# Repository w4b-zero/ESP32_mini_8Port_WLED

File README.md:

# ESP32_mini_8Port_WLED
<p align="center">
               
[<img src="https://img.shields.io/github/v/tag/w4b-zero/ESP32_mini_8Port_WLED?label=Relase&logo=data%3Aimage%2Fpng%3Bbase64%2CiVBORw0KGgoAAAANSUhEUgAAABgAAAAYCAYAAADgdz34AAABhGlDQ1BJQ0MgcHJvZmlsZQAAKJF9kT1Iw1AUhU9TtVIqHewg4pChOlkQFXHUKhShQqgVWnUweekfNDEkKS6OgmvBwZ%2FFqoOLs64OroIg%2BAPi6uKk6CIl3pcUWsR44fE%2Bzrvn8N59gNCoMs3qGgM03TYzqaSYy6%2BIoVf0IIgoAgjLzDJmJSkN3%2Fq6pz6quwTP8u%2F7s%2FrUgsWAgEg8wwzTJl4nntq0Dc77xDFWllXic%2BJRky5I%2FMh1xeM3ziWXBZ4ZM7OZOeIYsVjqYKWDWdnUiCeJ46qmU76Q81jlvMVZq9ZY6578hZGCvrzEdVpDSGEBi5AgQkENFVRhI0G7ToqFDJ0nffyDrl8il0KuChg55rEBDbLrB%2F%2BD37O1ihPjXlIkCXS%2FOM7HMBDaBZp1x%2Fk%2BdpzmCRB8Bq70tn%2BjAUx%2Fkl5va%2FEjILoNXFy3NWUPuNwBBp4M2ZRdKUhLKBaB9zP6pjzQfwuEV725tc5x%2BgBkaVbpG%2BDgEBgpUfaaz7t7O%2Bf2b09rfj%2FJPHJjkWAKcAAAAAlwSFlzAAAN1wAADdcBQiibeAAAAAd0SU1FB%2BcGAw8EJudd3BAAAAEvSURBVEjHtZYxTsQwEEXfRIgNzbZcBIkjQE2FqFIimmVPAFeggRPQoaViQwsNBfSIkwAS2k%2FjIBMSx86akSJFk8k8%2Fz%2BOFfjnsOZG0hQ4Arb9fCsEvAE3ZvYVTZE0lfSq%2BLiTtBWtQNIxcAV8AM9upV2xCey69%2B6BAzN7j1Fw5lb2GFE7k7Ry9fWQkqLD47Bkswtg7mr3gdsQpGgPO8rX35C9EKQYsKOQVLmrGIAsJJVDM3ho5Stv51RjZjLKooGZLP7YJem8R0GvRUlKPIue1jkWOiCT5sGhS64kzTJC5k1yw33%2BuSC163XtJ0tJSw9ymk1BLkir%2BfJnBjkgHQMuQ8VJkNQDMAkyqnksJMmWVMhaK4%2BA1Nma90DkbcUy6q8iEjIBToAd4AW4NLPP0DvfUiJxtCJLzP0AAAAASUVORK5CYII%3D&style=plastic">](https://github.com/w4b-zero/ESP32_mini_8Port_WLED/releases)
 &nbsp; 
 &nbsp; 
 &nbsp; 
 &nbsp; 
[![IMAGE_ALT](https://img.shields.io/github/languages/code-size/w4b-zero/ESP32_mini_8Port_WLED?style=plastic&logo=data%3Aimage%2Fpng%3Bbase64%2CiVBORw0KGgoAAAANSUhEUgAAABgAAAAYCAYAAADgdz34AAABhWlDQ1BJQ0MgcHJvZmlsZQAAKJF9kT1Iw0AcxV9TtSIVBTuIOASpgmBBVMRRq1CECqFWaNXB5NIvaNKQpLg4Cq4FBz8Wqw4uzro6uAqC4AeIq4uToouU%2BL%2Bk0CLWg%2BN%2BvLv3uHsHCNUi06y2cUDTbTMRi4qp9KoYeEUH%2FOjFEEZlZhlzkhRHy%2FF1Dx9f7yI8q%2FW5P0e3mrEY4BOJZ5lh2sQbxNObtsF5nzjE8rJKfE48ZtIFiR%2B5rnj8xjnnssAzQ2YyMU8cIhZzTaw0McubGvEUcVjVdMoXUh6rnLc4a8Uyq9%2BTvzCY0VeWuU5zEDEsYgkSRCgoo4AibERo1UmxkKD9aAv%2FgOuXyKWQqwBGjgWUoEF2%2FeB%2F8LtbKzs54SUFo0D7i%2BN8DAOBXaBWcZzvY8epnQD%2BZ%2BBKb%2FhLVWDmk%2FRKQwsfAT3bwMV1Q1P2gMsdoP%2FJkE3Zlfw0hWwWeD%2Bjb0oDfbdA15rXW30fpw9AkrqK3wAHh8BIjrLXW7y7s7m3f8%2FU%2B%2FsBa05ypE2o5wYAAAAJcEhZcwAADdcAAA3XAUIom3gAAAAHdElNRQfnBgMRBAFU7%2BcBAAABg0lEQVRIx72WsUtbURTGf%2FdhKOpmN5eSwdVOMYUWCkKhVOPgIM1f4JjRNWMnO5R2Lx1FJylth1QdBEFQ3MShVB0FkUihWvx1uYXweGmSl5g7nvu9%2B53vnPMdHgzzqHPqud2fn2rlf2%2BGFMEZcAl87pDLM%2BApsA88BqohhPVuFKjWu8DVI3ZMbah%2F1GoWNumnpCGEX8A8sAN8yiJJ%2Bu1bJFkAdoGP6Z7kJfgdS%2FUwklwDr4BD4N0gCL4At8DFv3ECmkAJeNQKHMlZlgN1BqgA4xnT1XY6jtTXffioHtVkKwghTA%2FavMl9b4ekRd6EuqWupmS%2FVb%2BrE7kJ1MloljLwLYX5CjwBtiOu58YU1RO1qb5og3muXqk%2F1Klemox6rN6opQ6JlCLuuBeCBFgDCkBNLbT5sADUIm4tT5lW1Dt1Ux1N3T1QN6Jh3%2FTqg9bL5bh236fiH2J8OY%2FR0oBZtZyKldXZQTm5kbF39vox2khGFktAMed7i8BZJ5lH5j%2Bn6suh%2Fqn8BbHck7yUqD2nAAAAAElFTkSuQmCC)](https://github.com/w4b-zero/ESP32_mini_8Port_WLED/archive/refs/heads/main.zip) <br> 
 &nbsp; 
 &nbsp; 

</p>

### Eliminated short circuit, corrected schematic & PCB!

PCB and KiCad-Files for a 8Port WLED ESP32_mini Board<br>
</a> <br>
<ul>
<li>Gerber Files</li>
<li>KiCad 7 Project Files</li>
<li>included used Library Files where not in official KiCad-Library for KiCad 7</li>
  </ul>
<br>

## KiCad Symbol Librarys

<ul>
<li>button:SW_PUSH-12mm</li>
<li>button:SW_PUSH-12mm_roundKnob</li>
<li>button:SW_PUSH-12mm_squareKnob</li>
<li>eec:TSOP38238</li>
<li>ESP32_mini:mini_esp32</li>
<li>wemos_mini:WeMos_D1_mini</li>
  </ul>
<br> 

## KiCad Footprints inkl. 3D-Models

<ul>
<li>button:SW_PUSH-12mm</li>
<li>button:SW_PUSH-12mm_roundKnob</li>
<li>button:SW_PUSH-12mm_squareKnob</li>
<li>eec:Vishay_Semiconductors-TSOP38238-Manufacturer_Recommended</li>
<li>ESP32_mini:ESP32_mini-only-connector</li>
<li>ESP32_mini:ESP32_mini-with-pin-header</li>
<li>ESP32_mini:ESP32_mini-with-pin-header-and-connector</li>
<li>logocircuit:brain</li>
<li>logocircuit:brainbig</li>
<li>logocircuit:WLED_Logo_micro</li>
<li>logocircuit:WLED_Logo_micro_cu</li>
<li>logocircuit:WLED_Logo_mini</li>
<li>logocircuit:zeroTM_Logo</li>
<li>logocircuit:zeroTM_Logo_layerB</li>
<li>logocircuit:zeroTM_Logo_micro</li>
<li>logocircuit:zeroTM_Logo_micro_cu</li>
<li>logocircuit:zeroTM_Logo_mini</li>
<li>mounts:MountingHole_3.2mm_M3_Pad_Via</li>
<li>Terminal_dg306:TerminalBlock_RND_205-00045_1x02_P5.00mm_Horizontal</li>
<li>Terminal_dg306:TerminalBlock_RND_205-00046_1x03_P5.00mm_Horizontal</li>
<li>Terminal_dg306:TerminalBlock_RND_205-00047_1x04_P5.00mm_Horizontal</li>
<li>Terminal_dg306:TerminalBlock_RND_205-00048_1x05_P5.00mm_Horizontal</li>
<li>Terminal_dg306:TerminalBlock_RND_205-00049_1x06_P5.00mm_Horizontal</li>
<li>Terminal_dg306:TerminalBlock_RND_205-00050_1x07_P5.00mm_Horizontal</li>
<li>Terminal_dg306:TerminalBlock_RND_205-00051_1x08_P5.00mm_Horizontal</li>
<li>Terminal_dg306:TerminalBlock_RND_205-00052_1x09_P5.00mm_Horizontal</li>
<li>Terminal_dg306:TerminalBlock_RND_205-00053_1x10_P5.00mm_Horizontal</li>
<li>Terminal_dg306:TerminalBlock_RND_205-00054_1x11_P5.00mm_Horizontal</li>
<li>Terminal_dg306:TerminalBlock_RND_205-00055_1x12_P5.00mm_Horizontal</li>
<li>wemos-d1-mini:wemos-d1-mini-connectors-only</li>
<li>wemos-d1-mini:wemos-d1-mini-embedded</li>
<li>wemos-d1-mini:wemos-d1-mini-with-pin-header</li>
  <li>wemos-d1-mini:wemos-d1-mini-with-pin-header-and-connector</li>
  </ul>
<br>

## WLED-Board for ESP23 mini in use

#### Test
<br>

#### Connected
<br>

#### Matrix with 2048 WS2812 LEDs
<br>

#### ESP32_mini_8Port_WLED drived the Matrix
<br>
Firmware: WLED https://github.com/Aircoookie/WLED <br>
Leds: 2048 (256 to each port)

## Youtube Videos

#### 2048 WS2812b Led's. first test.<br>

#### 2048 WS2812b Led's - capture the screen test.<br>

#### 2048 WS2812b Led's - colorscroll<br>

Firmware: WLED https://github.com/Aircoookie/WLED <br>
PC Software: Jinx! http://www.live-leds.de/ <br>
Leds: 2048 (512 to each port) <br>
<br>

## My Discord Server

 <br>

<br>

##  usefull Links!! 

WLED Projectpage:  https://kno.wled.ge/ <br>

Join the WLED Discord server to discuss everything about WLED!<br>
 <br>

Check out the WLED [Discourse forum](https://wled.discourse.group)! <br> 

Firmware: WLED Sourcecode https://github.com/Aircoookie/WLED <br>

PCB Manufacturing & Assembly: JLBPCB https://jlcpcb.com/

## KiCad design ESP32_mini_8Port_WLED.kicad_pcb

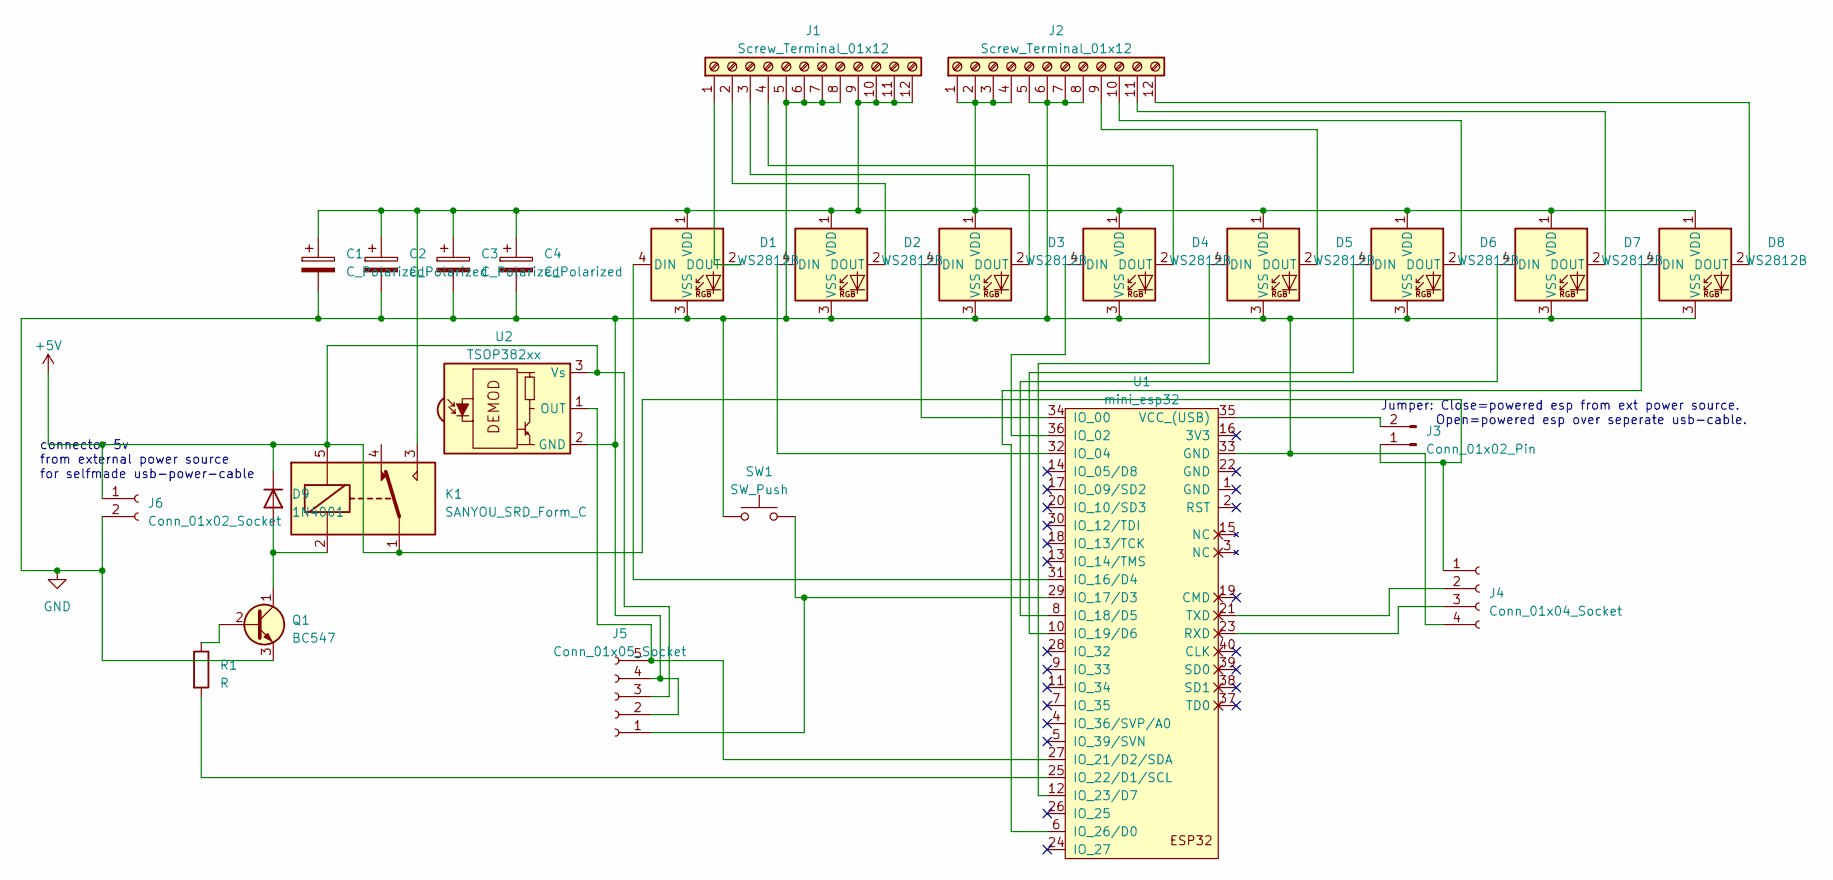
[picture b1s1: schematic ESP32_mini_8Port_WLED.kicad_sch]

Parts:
C1, C2: C_Polarized; CP_Radial_D8.0mm_P3.50mm
C3, C4: C_Polarized; CP_Radial_D16.0mm_P7.50mm
D1, D2, D3, D4, D5, D6, D7, D8: WS2812B; LED_WS2812B_PLCC4_5.0x5.0mm_P3.2mm
D9: 1N4001; D_DO-41_SOD81_P10.16mm_Horizontal
J1, J2: Screw_Terminal_01x12; TerminalBlock_RND_205-00055_1x12_P5.00mm_Horizontal
J3: Conn_01x02_Pin; PinHeader_1x02_P2.54mm_Vertical
J4: Conn_01x04_Socket; PinSocket_1x04_P2.54mm_Vertical
J5: Conn_01x05_Socket; PinSocket_1x05_P2.54mm_Vertical
J6: Conn_01x02_Socket; PinSocket_1x02_P2.54mm_Vertical
K1: SANYOU_SRD_Form_C; Relay_SPDT_SANYOU_SRD_Series_Form_C
Q1: BC547; TO-92L_Inline
R1: R; R_Axial_DIN0309_L9.0mm_D3.2mm_P12.70mm_Horizontal
SW1: SW_Push; SW_PUSH-12mm_roundKnob
U1: mini_esp32; ESP32_mini-with-pin-header-and-connector
U2: TSOP382xx; Vishay_MINICAST-3Pin

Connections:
+5V: D9.1 (K), J3.1, J4.1, J5.3, J6.1, K1.1, K1.5, U2.3 (Vs); also elsewhere on the board
GND: C1.2, C2.2, C3.2, C4.2, D1.3 (VSS), D2.3 (VSS), D3.3 (VSS), D4.3 (VSS), D5.3 (VSS), D6.3 (VSS), D7.3 (VSS), D8.3 (VSS), J1.5, J1.6, J1.7, J1.8, J2.5, J2.6, J2.7, J2.8, J4.4, J5.2, J5.4, J6.2, Q1.3 (E), SW1.1, U1.33 (GND), U2.2 (GND); also elsewhere on the board
unnamed: D1.4 (DIN), U1.31 (IO_16/D4)
unnamed: D1.2 (DOUT), J1.1
unnamed: C1.1, C2.1, C3.1, C4.1, D1.1 (VDD), D2.1 (VDD), D3.1 (VDD), D4.1 (VDD), D5.1 (VDD), D6.1 (VDD), D7.1 (VDD), D8.1 (VDD), J1.9, J1.10, J1.11, J1.12, J2.1, J2.2, J2.3, J2.4, K1.3
unnamed: D2.4 (DIN), U1.32 (IO_04)
unnamed: D2.2 (DOUT), J1.2
unnamed: D3.4 (DIN), U1.34 (IO_00)
unnamed: D3.2 (DOUT), J1.3
unnamed: D4.4 (DIN), U1.36 (IO_02)
unnamed: D4.2 (DOUT), J1.4
unnamed: D5.4 (DIN), U1.12 (IO_23/D7)
unnamed: D5.2 (DOUT), J2.9
unnamed: D6.4 (DIN), U1.10 (IO_19/D6)
unnamed: D6.2 (DOUT), J2.10
unnamed: D7.4 (DIN), U1.8 (IO_18/D5)
unnamed: D7.2 (DOUT), J2.11
unnamed: D8.4 (DIN), U1.6 (IO_26/D0)
unnamed: D8.2 (DOUT), J2.12
unnamed: D9.2 (A), K1.2, Q1.1 (C)
unnamed: J3.2, U1.35 (VCC_(USB))
unnamed: J4.2, U1.21 (TXD)
unnamed: J4.3, U1.23 (RXD)
unnamed: J5.1, SW1.2, U1.29 (IO_17/D3)
unnamed: J5.5, U1.27 (IO_21/D2/SDA), U2.1 (OUT)
unnamed: Q1.2 (B), R1.1
unnamed: R1.2, U1.25 (IO_22/D1/SCL)

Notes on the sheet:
Jumper: Close=powered esp from ext power source. Open=powered esp over seperate usb-cable.
connector 5v from external power source for selfmade usb-power-cable

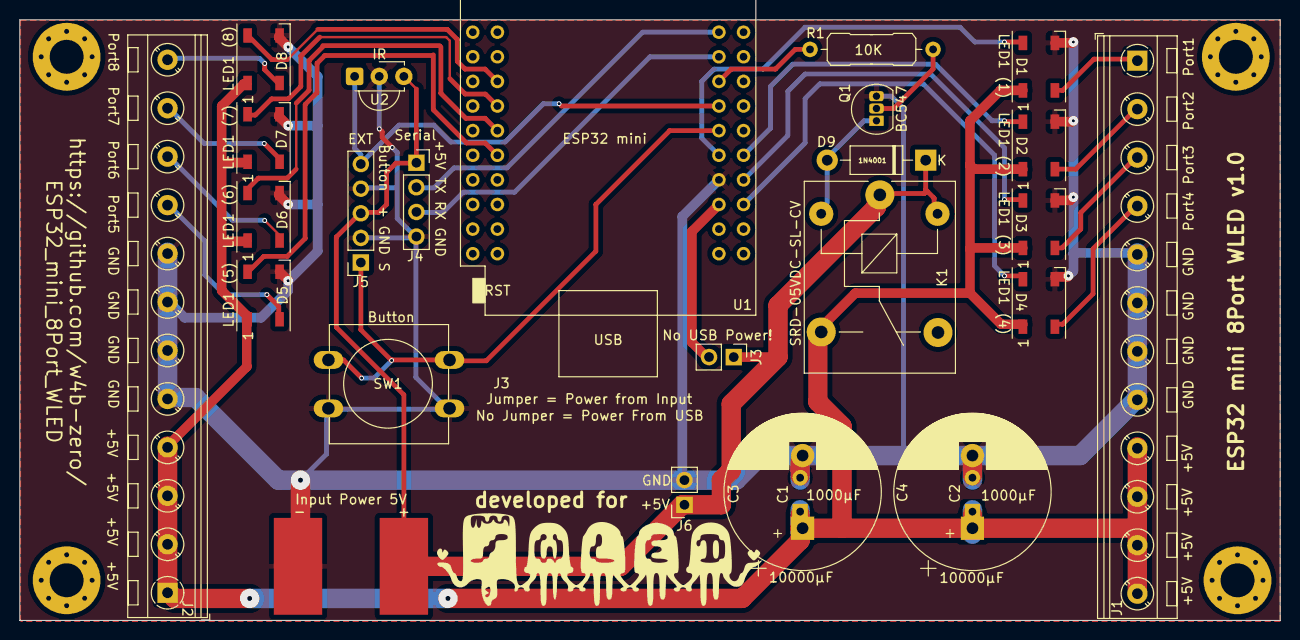
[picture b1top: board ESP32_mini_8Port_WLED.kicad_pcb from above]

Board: 2 copper layers, 130.0 x 62.0 mm, 27 parts (0 on the bottom side), 27 nets.

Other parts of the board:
+: SolderWirePad_1x01_SMD_5x10mm
-: SolderWirePad_1x01_SMD_5x10mm

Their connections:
+5V: +.1; also elsewhere on the board
GND: -.1; also elsewhere on the board

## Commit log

2023-06-05 added compiled firmware
    v0.14.0-b2 "Hoshi"
2023-06-14 Add Schema Image
2023-07-01 PCB Error: IR sensor has a short circuit!
2023-07-02 Mistake corrected!
    Eliminated short circuit, corrected schematic & PCB.
